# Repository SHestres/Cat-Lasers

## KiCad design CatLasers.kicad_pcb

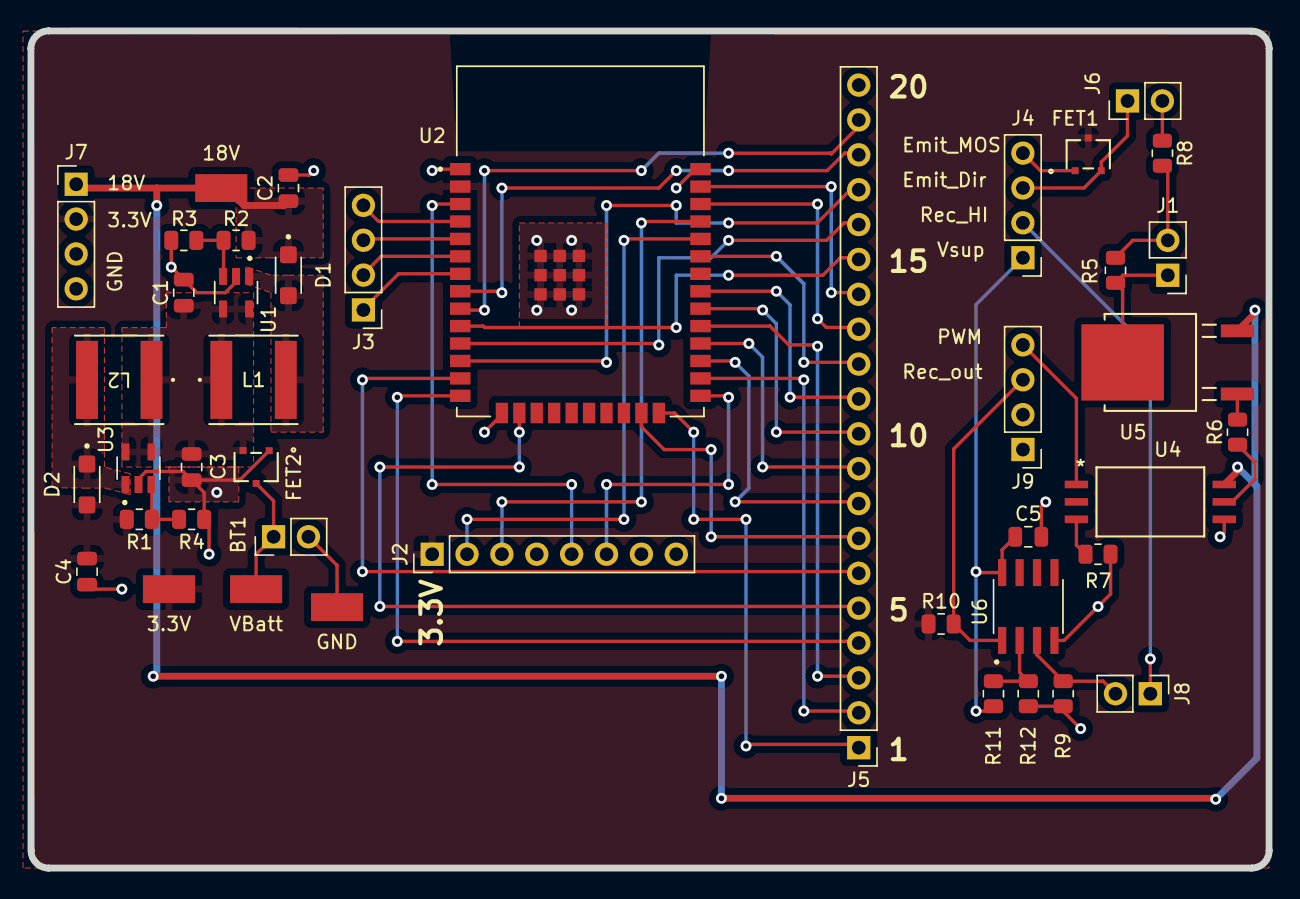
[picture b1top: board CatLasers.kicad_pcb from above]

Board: 2 copper layers, 90.2 x 61.0 mm, 43 parts (0 on the bottom side), 49 nets.

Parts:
3.3V: 3.3V; TestPoint_KEYSTONE_5019
18V: 18V; TestPoint_KEYSTONE_5019
BT1: Battery; PinHeader_1x02_P2.54mm_Vertical
C1, C3: 1uF; C_0805_2012Metric
C2, C4: 4.7 uF; C_0805_2012Metric
C5: .1 uF; C_0805_2012Metric
D1, D2: D_Schottky; SODFL3618X110N
FET1, FET2: SSM3J328R; SOT-23F_TOS
GND: GND; TestPoint_KEYSTONE_5019
J1: Piezzo; PinHeader_1x02_P2.54mm_Vertical
J2: Programmer; PinHeader_1x08_P2.54mm_Vertical
J3, J4, J9: Conn_01x04; PinHeader_1x04_P2.54mm_Vertical
J5: Conn_01x20; PinHeader_1x20_P2.54mm_Vertical
J6: IR Emitter; PinHeader_1x02_P2.54mm_Vertical
J7: Power Jumper; PinHeader_1x04_P2.54mm_Vertical
J8: IR Receiver; PinHeader_1x02_P2.54mm_Vertical
L1, L2: 10uH; IND_TAIYO_NR6028_TAY
R1: 3.3HI; R_0805_2012Metric
R2: 18HI; R_0805_2012Metric
R3: 18LO; R_0805_2012Metric
R4: 3.3LO; R_0805_2012Metric
R5, R6, R8, R9, R10, R11, R12: R; R_0805_2012Metric
R7: 120Ω; R_0805_2012Metric
U1, U3: MIC2288YD5-TR; SOT95P280X100-5N
U2: ESP32-WROOM-32E_(4MB_HIGH_TEMP); XCVR_ESP32-WROOM-32E_(4MB_HIGH_TEMP)
U4: UCC23313DWYR; SOIC6_DWY_TEX
U5: RD3L01BATTL1; RD3L01BATTL1_ROM
U6: LM293DRE4; SOIC127P599X175-8N
VBatt: VBatt; TestPoint_KEYSTONE_5019

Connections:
3.3V: 3.3V.TP (1), C4.2, D2.1 (K), FET1.3, J2.1, J7.2, R1.2, R10.1, U2.2 (3V3)
18V: 18V.TP (1), C2.1, D1.2 (C), J7.1, R2.1, U4.6 (VCC), U5.3 (Source)
/Buzzer/PWM: J9.4, U4.1 (ANODE)
/IR Emitter + Receiver/Emit_Direct: FET1.2, J4.3, J6.1
/IR Emitter + Receiver/Emit_MOS: FET1.1, J4.4
/IR Emitter + Receiver/RecSup: J4.2, J8.1
/IR Emitter + Receiver/Rec_out: J9.3, R10.2, U6.1 (1OUT)
/IR Emitter + Receiver/Vrec: J8.2, R9.1, U6.3 (1IN+)
/IR Emitter + Receiver/Vref: R11.2, R12.1, U6.2 (1IN-)
/IR Emitter + Receiver/Vsup: C5.1, J4.1, R11.1, U6.8 (VCC)
/PowerSupply/FB_3.3: R1.1, R4.2, U3.3 (FB)
/PowerSupply/FB_18: R2.2, R3.1, U1.3 (FB)
/PowerSupply/SW_3.3: D2.2 (A), L2.2, U3.1 (SW)
/PowerSupply/SW_18: D1.1 (A), L1.2, U1.1 (SW)
/PowerSupply/VBatt: BT1.1 (+), FET2.3, VBatt.TP
/PowerSupply/Vin: C1.1, C3.2, FET2.2, L1.1, L2.1, U1.4 (EN), U1.5 (VIN), U3.4 (EN), U3.5 (VIN)
GND: BT1.2 (-), C1.2, C2.2, C3.1, C4.1, C5.2, FET2.1, GND.TP (1), J1.2, J2.4, J5.20, J7.3, J7.4, R3.2, R4.1, R5.2, R7.2, R8.2, R9.2, R12.2, U1.2 (GND), U2.1 (GND), U2.15 (GND), U2.38 (GND), U2.39_1 (GND), U2.39_2 (GND), U2.39_3 (GND), U2.39_4 (GND), U2.39_5 (GND), U2.39_6 (GND), U2.39_7 (GND), U2.39_8 (GND), U2.39_9 (GND), U3.2 (GND), U4.4 (VEE), U6.4 (GND)
unnamed: J1.1, R5.1, U5.2 (Drain)
unnamed: J2.2, U2.34 (RXD0)
unnamed: J2.3, U2.35 (TXD0)
unnamed: J2.5, U2.3 (EN)
unnamed: J2.6, U2.25 (IO0)
unnamed: J3.1, U2.7 (IO35)
unnamed: J3.2, U2.6 (IO34)
unnamed: J3.3, U2.5 (SENSOR_VN)
unnamed: J3.4, U2.4 (SENSOR_VP)
unnamed: J5.1, U2.24 (IO2)
unnamed: J5.2, U2.26 (IO4)
unnamed: J5.3, U2.29 (IO5)
unnamed: J5.4, U2.14 (IO12)
unnamed: J5.5, U2.16 (IO13)
unnamed: J5.6, U2.13 (IO14)
unnamed: J5.7, U2.23 (IO15)
unnamed: J5.8, U2.27 (IO16)
unnamed: J5.9, U2.28 (IO17)
unnamed: J5.10, U2.30 (IO18)
unnamed: J5.11, U2.31 (IO19)
unnamed: J5.12, U2.33 (IO21)
unnamed: J5.13, U2.36 (IO22)
unnamed: J5.14, U2.37 (IO23)
unnamed: J5.15, U2.10 (IO25)
unnamed: J5.16, U2.11 (IO26)
unnamed: J5.17, U2.12 (IO27)
unnamed: J5.18, U2.8 (IO32)
unnamed: J5.19, U2.9 (IO33)
unnamed: J6.2, R8.1
unnamed: R7.1, U4.3 (CATHODE)
unnamed: R6.1, U4.5 (VOUT)
unnamed: R6.2, U5.1 (Gate)

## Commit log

2023-09-14 Power Supply Schematic
2023-09-17 Setup XIDE
2023-09-17 2 voltage regulators + new diodes
2023-09-17 Capacitors chosen and footprints assigned
2023-09-18 Resistors named, footprints assigned
2023-09-18 Project footprint library added
2023-09-18 Inductor chosen and footprint assigned
2023-09-18 Testpoints added to power supply
2023-09-19 Buzzer sheet 1st draft finished
2023-09-19 Gate Driver resistor chosen and footprint added
2023-09-25 MCU Pin Headers added and footprints assigned
2023-09-25 IR Emitter circuit
    Circuit added and all footprints assigned
2023-09-26 MCU switched to ESP32-WROOM
    First pass at programmer pin connections
    Footprints assigned
2023-09-26 Wired MCU jumpers
    All MCU pins are sent directly to jumpers. This will double as testpoints and a way for me to easily rewire the test board.
    Footprints also assigned
2023-09-26 Added power jumper
2023-09-26 Moved IR Emitter and Receiver to separate sheet
2023-09-27 IR Receiver and Comparator
2023-09-27 Some cleanup
2023-09-27 Corrected power supply PMOS
2023-09-27 Remaining Footprints Assigned
2023-09-27 Annotations
2023-09-27 Components on PCB, all warnings and error fixed
2023-09-27 Added Voltage stabalizing capacitors
2023-09-27 Revert "Added Voltage stabalizing capacitors"
    This reverts commit 707a44219213f2b52e07c81fee0218c85384a0bb.
2023-09-27 Power Supply Net Labels
2023-09-28 Power Supply Layout
2023-09-28 Piezzo Layout
2023-09-28 MCU Layout
2023-09-28 Emitter, Receiver, and board outline
2023-09-28 Routing Draft Finished
2023-09-28 DRC Pass
2023-09-28 Extra Silk Screens
2023-09-28 Board Shortened
    The price jumps significantly (some 400%) when the board crosses the threshold of 100mm in length
2023-09-28 html BOM
2023-10-03 Gerber Files generateed and Fixed
